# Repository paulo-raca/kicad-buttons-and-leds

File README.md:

# kicad-buttons-and-leds
Small PCB with 8 buttons and 8 leds

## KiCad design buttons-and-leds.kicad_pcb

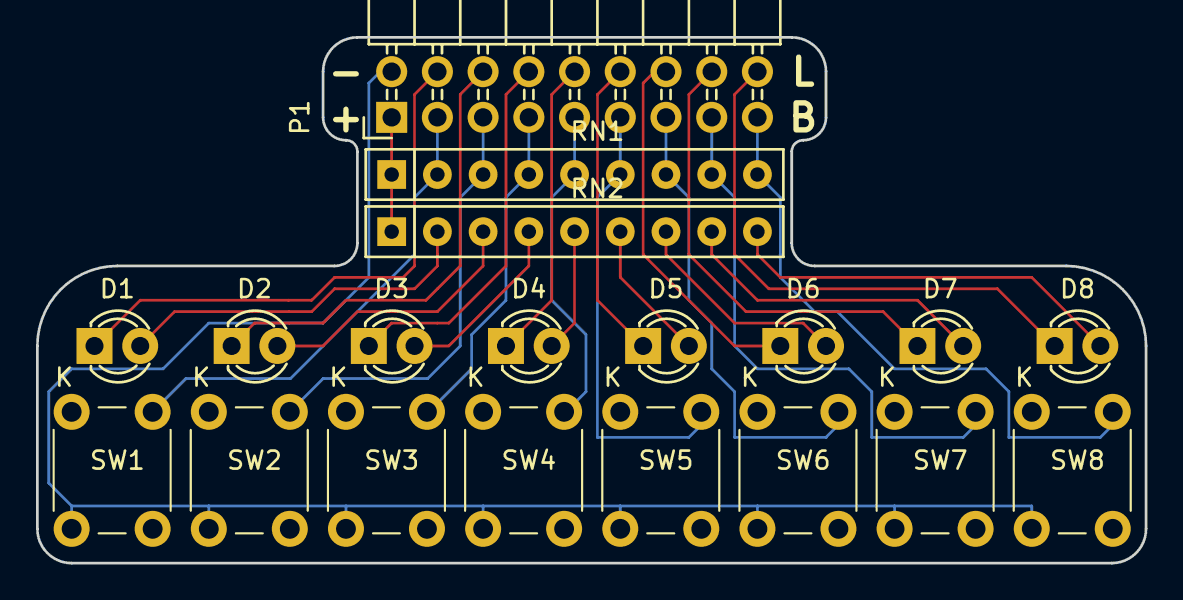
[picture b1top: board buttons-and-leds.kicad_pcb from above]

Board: 2 copper layers, 61.6 x 29.2 mm, 19 parts (0 on the bottom side), 26 nets.

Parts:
D1, D2, D3, D4, D5, D6, D7, D8: LED; LED-3MM
P1: CONN_02X09; Pin_Header_Angled_2x09
RN1, RN2: R_Network08; Resistor_Array_SIP9
SW1, SW2, SW3, SW4, SW5, SW6, SW7, SW8: SW_Push; SW_PUSH_6mm

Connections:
GND: P1.2, SW1.1, SW2.1, SW3.1, SW4.1, SW5.1, SW6.1, SW7.1, SW8.1
unnamed: D1.1, P1.4
unnamed: D1.2, RN2.2
unnamed: D2.1, P1.6
unnamed: D2.2, RN2.3
unnamed: D3.1, P1.8
unnamed: D3.2, RN2.4
unnamed: D4.1, P1.10
unnamed: D4.2, RN2.5
unnamed: D5.1, P1.12
unnamed: D5.2, RN2.6
unnamed: D6.1, P1.14
unnamed: D6.2, RN2.7
unnamed: D7.1, P1.16
unnamed: D7.2, RN2.8
unnamed: D8.1, P1.18
unnamed: D8.2, RN2.9
unnamed: P1.3, RN1.2, SW1.2
unnamed: P1.5, RN1.3, SW2.2
unnamed: P1.7, RN1.4, SW3.2
unnamed: P1.9, RN1.5, SW4.2
unnamed: P1.11, RN1.6, SW5.2
unnamed: P1.13, RN1.7, SW6.2
unnamed: P1.15, RN1.8, SW7.2
unnamed: P1.17, RN1.9, SW8.2
VCC: P1.1, RN1.1, RN2.1

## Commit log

2017-08-04 Smaller and prettier
2017-09-15 Oops... There are a few Missing wires!
